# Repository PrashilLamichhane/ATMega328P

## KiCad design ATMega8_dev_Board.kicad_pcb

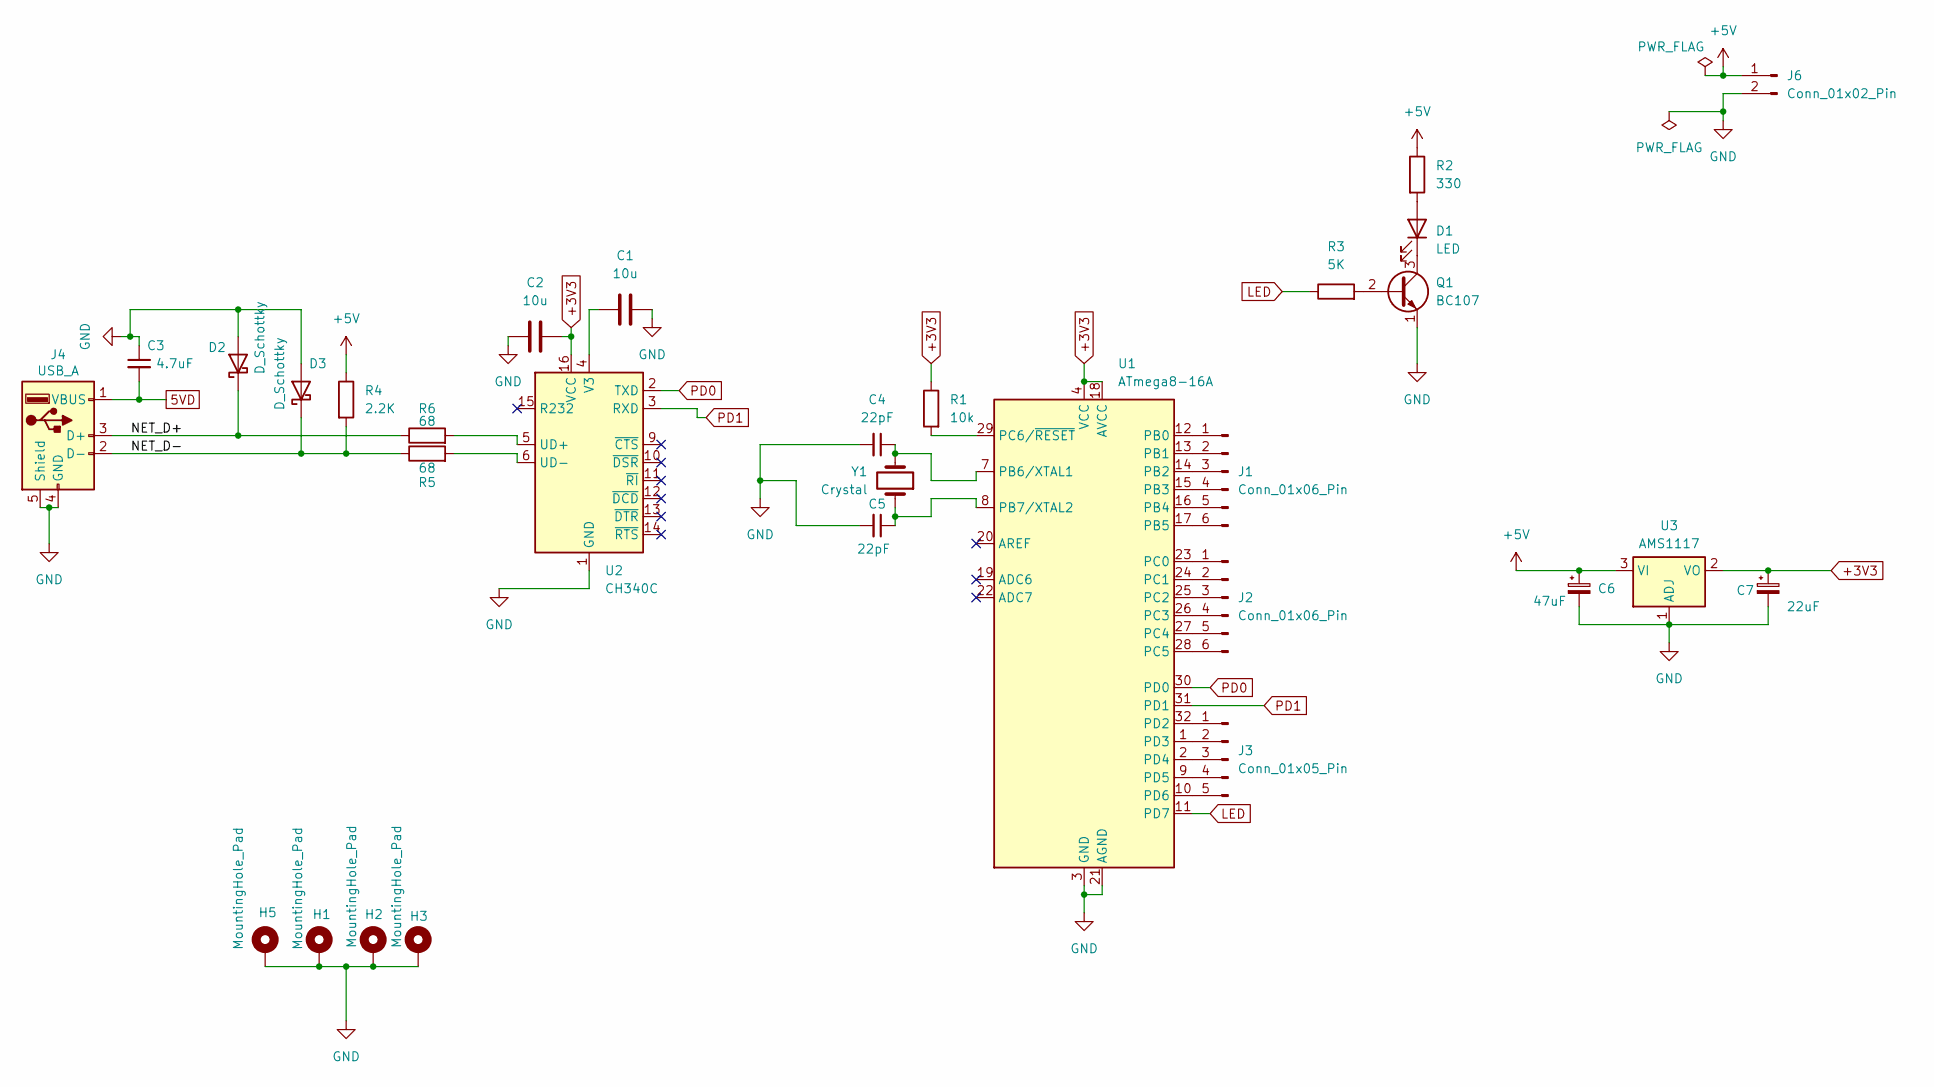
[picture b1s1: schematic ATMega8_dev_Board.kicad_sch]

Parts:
C1, C2: 10u; C_0805_2012Metric
C3: 4.7uF; C_1206_3216Metric
C4, C5: 22pF; C_0805_2012Metric
C6: 47uF; C_1210_3225Metric
C7: 22uF; C_1210_3225Metric
D1: LED; LED_0201_0603Metric
D2, D3: D_Schottky; D_SMA
H1, H2, H3, H5: MountingHole_Pad; MountingHole_3.2mm_M3_Pad_TopBottom
J1, J2: Conn_01x06_Pin; PinHeader_1x06_P1.27mm_Vertical
J3: Conn_01x05_Pin; PinHeader_1x06_P1.27mm_Vertical
J4: USB_A; USB_A_Molex_67643_Horizontal
J6: Conn_01x02_Pin; PinHeader_1x02_P1.27mm_Vertical
Q1: BC107; TO-18-3
R1: 10k; R_0603_1608Metric
R2: 330; R_0603_1608Metric
R3: 5K; R_0603_1608Metric
R4: 2.2K; R_0805_2012Metric
R5, R6: 68; R_0805_2012Metric
U1: ATmega8-16A; TQFP-32_7x7mm_P0.8mm
U2: CH340C; SOIC-16_3.9x9.9mm_P1.27mm
U3: AMS1117; SOT-223-3_TabPin2
Y1: Crystal; Crystal_SMD_HC49-SD

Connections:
5VD: C3.2, J4.1 (VBUS)
+3V3: C2.1, C7.1, R1.1, U1.4 (VCC), U1.6 (VCC), U1.18 (AVCC), U2.16 (VCC), U3.2 (VO)
+5V: C6.1, J6.1, R2.1, R4.1, U3.3 (VI)
/NET_D+: D2.1 (K), J4.3 (D+), R5.1
/NET_D-: D3.1 (K), J4.2 (D-), R4.2, R6.1
GND: C1.2, C2.2, C3.1, C4.2, C5.2, C6.2, C7.2, D2.2 (A), D3.2 (A), H1.1, H2.1, H3.1, H5.1, J4.4 (GND), J4.5 (Shield), J6.2, Q1.1 (E), U1.3 (GND), U1.5 (GND), U1.21 (AGND), U2.1 (GND), U3.1 (ADJ)
LED: R3.1, U1.11 (PD7)
unnamed: D1.2 (A), R2.2
unnamed: D1.1 (K), Q1.3 (C)
unnamed: J1.1, U1.12 (PB0)
unnamed: J1.2, U1.13 (PB1)
unnamed: J1.3, U1.14 (PB2)
unnamed: J1.4, U1.15 (PB3)
unnamed: J1.5, U1.16 (PB4)
unnamed: J1.6, U1.17 (PB5)
unnamed: J2.1, U1.23 (PC0)
unnamed: J2.2, U1.24 (PC1)
unnamed: J2.3, U1.25 (PC2)
unnamed: J2.4, U1.26 (PC3)
unnamed: J2.5, U1.27 (PC4)
unnamed: J2.6, U1.28 (PC5)
unnamed: J3.1, U1.32 (PD2)
unnamed: J3.2, U1.1 (PD3)
unnamed: J3.3, U1.2 (PD4)
unnamed: J3.4, U1.9 (PD5)
unnamed: J3.5, U1.10 (PD6)
unnamed: Q1.2 (B), R3.2
unnamed: C4.1, U1.7 (PB6/XTAL1), Y1.2
unnamed: C5.1, U1.8 (PB7/XTAL2), Y1.1
unnamed: R1.2, U1.29 (PC6/~RESET)
unnamed: R5.2, U2.5 (UD+)
unnamed: R6.2, U2.6 (UD-)
unnamed: C1.1, U2.4 (V3)
PD0: U1.30 (PD0), U2.2 (TXD)
PD1: U1.31 (PD1), U2.3 (RXD)

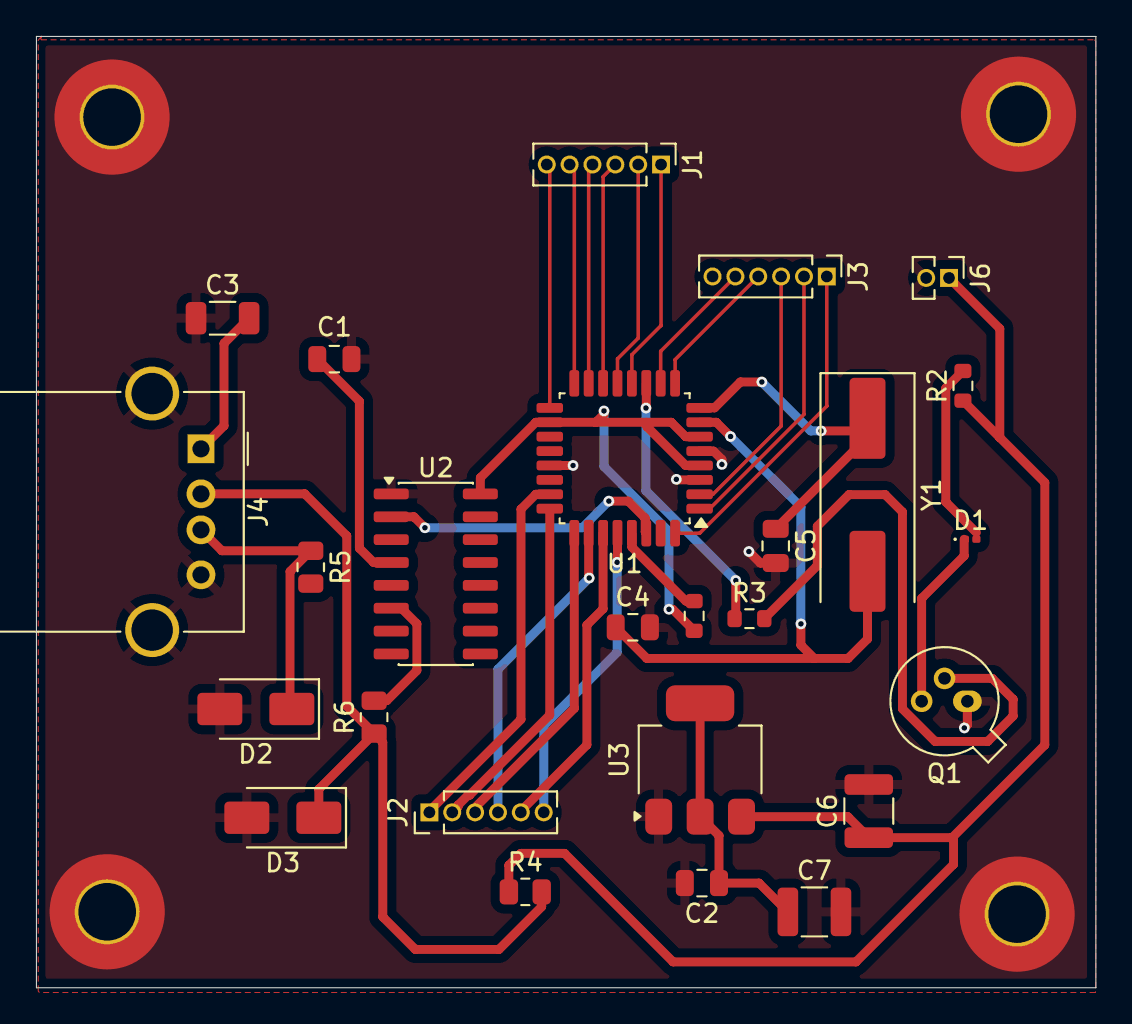
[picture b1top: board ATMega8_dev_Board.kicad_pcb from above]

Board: 2 copper layers, 58.9 x 52.8 mm, 30 parts (0 on the bottom side), 35 nets.
